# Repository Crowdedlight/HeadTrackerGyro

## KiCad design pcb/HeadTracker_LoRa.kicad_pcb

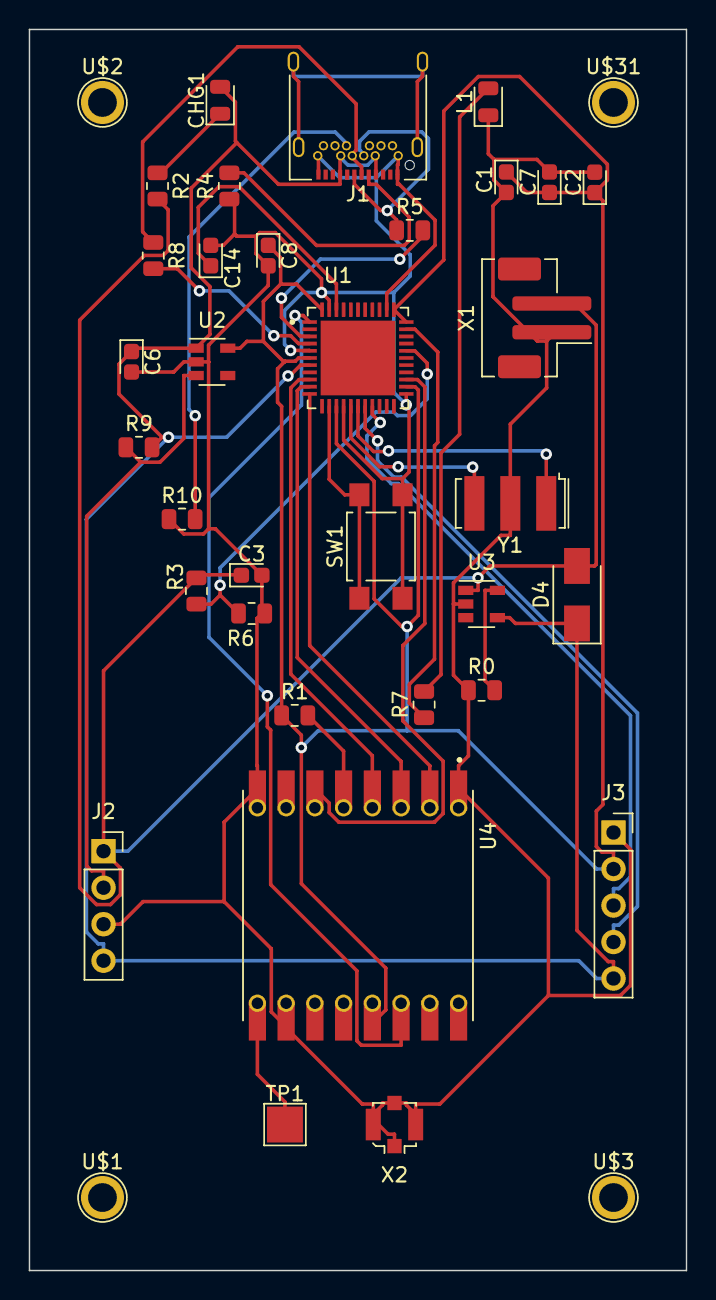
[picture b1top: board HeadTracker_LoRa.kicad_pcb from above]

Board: 2 copper layers, 45.7 x 86.4 mm, 37 parts (0 on the bottom side), 29 nets.

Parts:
C1, C3, C6, C8: 10 uF; CP_EIA-1608-08_AVX-J
C2, C7, C14: 1 uF; CP_EIA-1608-08_AVX-J
CHG1: Orange; D_0805_2012Metric
D4: MBR120; D_SMA
J1: USB_C_Receptacle_USB2.0; USB_C_Receptacle_Amphenol_12401548E4-2A
J2: Conn_01x04; PinSocket_1x04_P2.54mm_Vertical
J3: Conn_01x05; PinSocket_1x05_P2.54mm_Vertical
L1: RED; D_0805_2012Metric
R0: 2K; R_0805_2012Metric
R1, R9: 100k; R_0805_2012Metric
R2: 1K; R_0805_2012Metric
R3, R6: 10k; R_0805_2012Metric
R4, R10: 5.1K; R_0805_2012Metric
R5, R8: 22; R_0805_2012Metric
R7: 2.2K; R_0805_2012Metric
SW1: SPST_TACT-KMR2; SW_SPST_TL3305A
TP1: ANT; TestPoint_Pad_2.5x2.5mm
U1: ATMEGA32U4-MU; QFN50P700X700X100-45N
U2: AP2112K-3.3; SOT-23-5
U3: MCP73831-2-OT; SOT-23-5
U4: RFM69HCW; XCVR_RFM98W-433S2
U$1, U$2, U$3, U$31: MOUNTINGHOLE2.5; TestPoint_Plated_Hole_D2.0mm
X1: JSTPH; JST_PH_B2B-PH-SM4-TB_1x02-1MP_P2.00mm_Vertical
X2: ANTENNA_U.FL; U.FL_Molex_MCRF_73412-0110_Vertical
Y1: 8MHz Crystal; Resonator_SMD-3Pin_7.2x3.0mm

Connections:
+3V3: C1.1, C2.1, C7.1, C8.1, J3.2, R1.1, U1.6 (UCAP), U1.14 (VCC), U1.24 (AVCC), U1.33 (PE2(~HWB~{)), U1.34 (VCC), U1.44 (AVCC), U2.5 (VOUT), U4.13 (3.3V)
/9: R3.2, R6.1, U1.29 (PB5(PCINT5/OC1A/~OC4B~{/ADC))
/13: R7.1, U1.32 (PC7(ICP3/CLK0/OC4A))
/AREF: C14.1, U1.42 (AREF)
/CC1: J1.A5 (CC1), R4.2
/CC2: J1.B5 (CC2), R10.2
/D4_RST: U1.25 (PD4(ICP1/ADC8)), U4.6 (RESET)
/D8_CS: R1.2, U4.5 (NSS)
/D+: R8.2, U1.4 (D+)
/D-: R5.2, U1.3 (D-)
/DZ_IRQ: U1.1 ((INT6/AIN0)PE6), U4.14 (DIO0)
/EN: J2.2, R9.1, U2.3 (EN)
/MISO: U1.11 ((PDO/PCINT3/MISO)PB3), U4.2 (MISO)
/MOSI: U1.10 ((PDI/PCINT2/MOSI)PB2), U4.3 (MOSI)
/RST: SW1.1, U1.13 (~RESET~{)
/SCK: U1.9 ((PCINT1/SCLK)PB1), U4.4 (SCK)
/SCL: J3.4, U1.18 ((OC0B/SCL/INT0)PD0)
/SDA: J3.3, U1.19 ((SDA/INT1)PD1)
GND: C1.2, C2.2, C3.2, C6.2, C7.2, C8.2, C14.2, J1.A1 (GND), J1.A12 (GND), J1.B1 (GND), J1.B12 (GND), J2.3, J3.1, L1.1 (K), R0.1, R4.1, R6.2, R10.1, SW1.2 (S), U1.5 (UGND), U1.15 (GND), U1.23 (GND), U1.35 (GND), U1.43 (GND), U2.2 (GND), U3.2 (VSS), U4.1 (GND), U4.8 (GND), U4.10 (GND), X1.1, X2.1 (GND@0), X2.2 (GND@1), Y1.2
unnamed: CHG1.1 (K), R2.1
unnamed: J1.A6 (D+), J1.B6 (D+), R8.1
unnamed: J1.A7 (D-), J1.B7 (D-), R5.1
unnamed: L1.2 (A), R7.2
unnamed: R0.2, U3.5 (PROG)
unnamed: TP1.1, U4.9 (ANT)
unnamed: U1.16 (XTAL2), Y1.3
unnamed: U1.17 (XTAL1), Y1.1
VBAT: C3.1, D4.2 (A), J2.1, R2.2, R3.1, U3.1 (STAT), X1.2
VBUS: C6.1, CHG1.2 (A), D4.1 (K), J1.A4 (VBUS), J1.A9 (VBUS), J1.B4 (VBUS), J1.B9 (VBUS), J2.4, J3.5, R9.2, U1.7 (VBUS), U2.1 (VIN), U3.4 (VDD)

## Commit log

2023-02-15 initial
2023-02-15 removed leftovers
